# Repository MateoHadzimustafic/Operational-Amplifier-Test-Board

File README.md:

# Operational Amplifier Test Board

Short description of what this hardware project does.

## Overview

This Operational Amplifier Test Board is a versatile prototyping and evaluation platform designed for testing any standard 8-pin DIP op-amp using a universal DIP-8 socket. It features integrated test points for quick signal probing, banana connector inputs for easy compatibility with external DC bench power supplies, and breadboard-compatible pin headers for seamless circuit integration and experimentation. Built for rapid analog testing, debugging, and performance evaluation, this board simplifies op-amp characterization in both lab and prototyping environments.

## Current Status

Completed — Fully designed, built, tested, and validated.

## Features

- Bread board compatibility through the use of pin headers
- Test points for positive, negative, and output terminal
- Easy and efficient operational amplifier testing

## Repository Structure

- `hardware/` — schematic, PCB layout, and manufacturing files
- `bom/` — bill of materials and component notes
- `images/` — renders, diagrams, and photos

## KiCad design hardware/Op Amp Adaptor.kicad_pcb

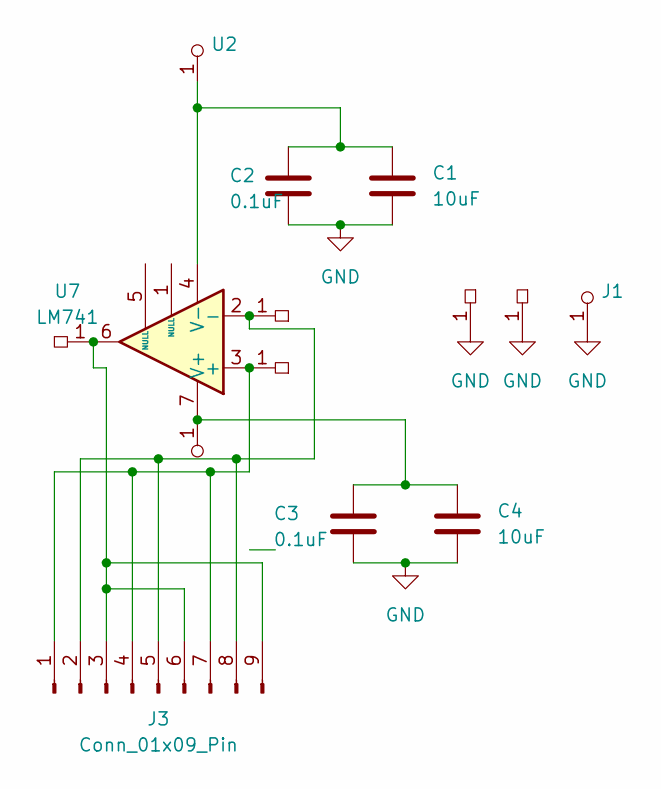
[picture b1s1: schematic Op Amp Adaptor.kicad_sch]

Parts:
C1, C4: 10uF; C_0805_2012Metric
C2, C3: 0.1uF; C_0805_2012Metric
J1: Banana_Jack_1Pin
J3: Conn_01x09_Pin; PinHeader_1x09_P2.54mm_Vertical
TP1, TP2, TP3, TP4, TP5: TestPoint_Keystone_5005-5009_Compact
U1, U2: Banana_Jack_1Pin
U7: LM741; Dip-8

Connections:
GND: C1.1, C2.1, C3.1, C4.1, J1.1, TP4.1, TP5.1
unnamed: J3.1, J3.4, J3.7, TP1.1, U7.3 (+)
unnamed: J3.2, J3.5, J3.8, TP3.1, U7.2 (-)
unnamed: J3.3, J3.6, J3.9, TP2.1, U7.6
unnamed: C3.2, C4.2, U1.1, U7.7 (V+)
unnamed: C1.2, C2.2, U2.1, U7.4 (V-)

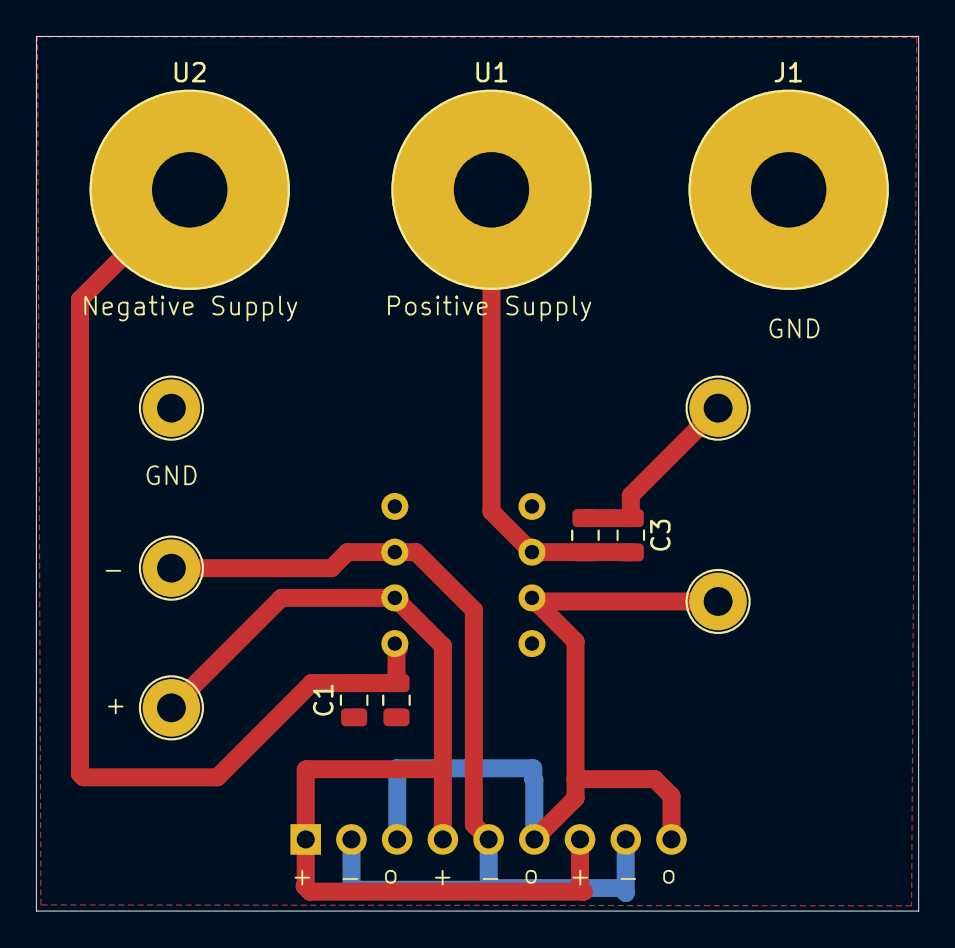
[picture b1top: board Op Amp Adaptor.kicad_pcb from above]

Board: 2 copper layers, 49.0 x 48.6 mm, 14 parts (1 on the bottom side), 6 nets.

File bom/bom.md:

| Designator               | Footprint                           | Quantity | Value           | LCSC Part # |
|--------------------------|-------------------------------------|----------|-----------------|--------------|
| J1, U1, U2               | Banana_Jack_1Pin                    | 3        | ~               |              |
| J2                       | PinHeader_1x03_P2.54mm_Vertical    | 1        | Conn_01x03_Pin  |              |
| TP1, TP2, TP3, TP4, TP5 | TestPoint_Keystone_5005-5009_Compact | 5      | ~               |              |
| U7                       | Dip-8                               | 1        | LM741           |              |

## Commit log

2026-04-30 Create testing
